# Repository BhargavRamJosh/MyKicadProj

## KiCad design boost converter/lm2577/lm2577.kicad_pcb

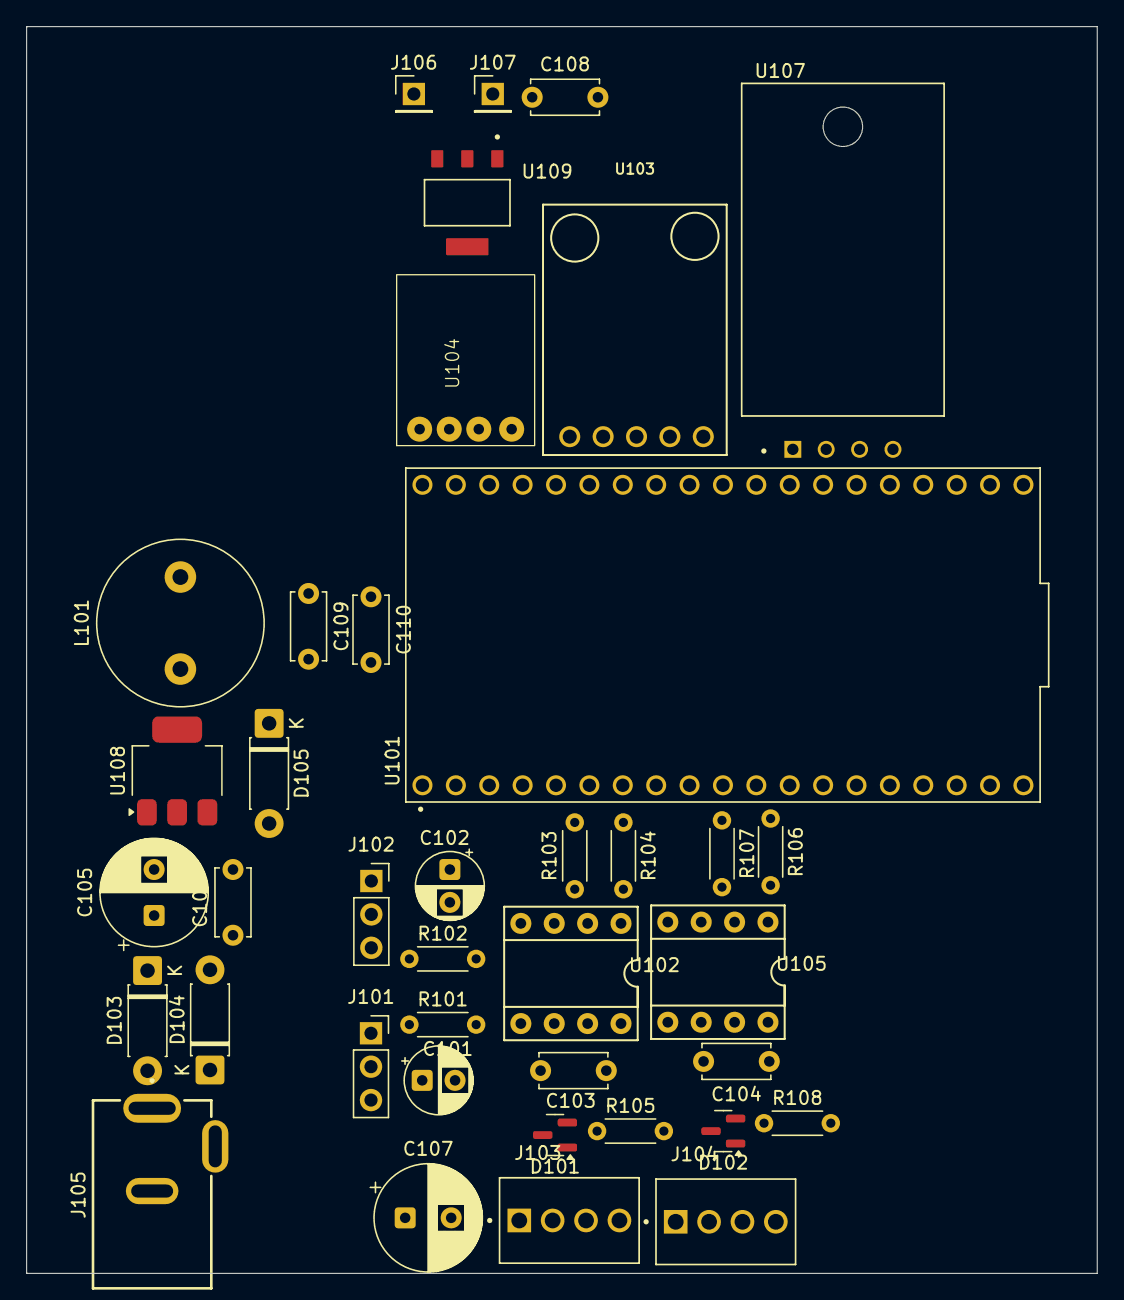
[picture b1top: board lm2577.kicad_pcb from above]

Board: 2 copper layers, 81.4 x 94.9 mm, 39 parts (0 on the bottom side), 24 nets, no tracks yet.

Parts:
C101: 10uF; CP_Radial_D5.0mm_P2.50mm
C102: 1uF; CP_Radial_D5.0mm_P2.50mm
C103, C104, C106, C110: 0.1uF; C_Disc_D5.0mm_W2.5mm_P5.00mm
C105: 100uF; CP_Radial_D8.0mm_P3.50mm
C107: 10uF; CP_Radial_D8.0mm_P3.50mm
C108: 10uF; C_Disc_D5.0mm_W2.5mm_P5.00mm
C109: 220uF; C_Disc_D5.0mm_W2.5mm_P5.00mm
D101, D102: SM712_SOT23; SOT-23
D103, D105: SS14; D_DO-41_SOD81_P7.62mm_Horizontal
D104: SMBJ15A; D_DO-41_SOD81_P7.62mm_Horizontal
J101, J102: Conn_01x03_Pin; PinSocket_1x03_P2.54mm_Vertical
J103, J104: Screw_Terminal_01x04; TE_282834-4
J105: DCJ200-10-A-XX-K_REVA; GCT_DCJ200-10-A-XX-K_REVA
J106, J107: Conn_01x01_Pin; PinHeader_1x01_P2.54mm_Vertical
L101: 22uH; L_Radial_D12.5mm_P7.00mm_Fastron_09HCP
R101, R102: 10K; R_Axial_DIN0204_L3.6mm_D1.6mm_P5.08mm_Horizontal
R103, R106: 3.9K; R_Axial_DIN0204_L3.6mm_D1.6mm_P5.08mm_Horizontal
R104, R107: 2K; R_Axial_DIN0204_L3.6mm_D1.6mm_P5.08mm_Horizontal
R105: 4.7K; R_Axial_DIN0204_L3.6mm_D1.6mm_P5.08mm_Horizontal
R108: 10k; R_Axial_DIN0204_L3.6mm_D1.6mm_P5.08mm_Horizontal
U101: NODEMCU-32S; MODULE_NODEMCU-32S
U102, U105: MAX485; DIL08
U103: ZC362800_
U104: BMP180; BMP180 breakout
U107: DHT22; XDCR_DHT22
U108: LM2596S-5; SOT-223-3_TabPin2
U109: AMS1117; SOT229P700X180-4N

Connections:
+5V: C103.1, C104.1, C107.1, C109.1, C110.1, J101.2, J102.2, J106.1, L101.2, U101.J1_19 (5V), U102.8 (VCC), U103.VCC, U105.8 (VCC), U109.3 (VI)
+12V: J103.1, J104.1
/ASoil: C101.2, R101.2, U101.J1_6 (IO35)
/Arain: C102.2, R102.2, U101.J1_5 (IO34)
/SCL: U101.J2_6 (IO21), U103.SCL
/SDA: U101.J2_3 (IO22), U103.SDA
/T&H: U101.J2_13 (IO4), U107.2 (DATA)
GND: C101.1, C102.1, C103.2, C104.2, C105.2, C106.2, C107.2, C108.2, C109.2, C110.2, D101.1 (A1), D101.3 (common), D102.1 (A1), D102.3 (common), D104.1 (K), D105.2 (A), J101.3, J102.3, J103.3, J103.4, J104.3, J104.4, J105.2, J105.3, R103.2, R105.2, R106.1, R108.2, U101.J1_14 (GND), U101.J2_1 (GND), U101.J2_7 (GND), U102.5 (GND), U102.6 (A), U103.GND, U105.5 (GND), U105.6 (A), U107.4 (GND), U108.3 (GND), U109.1 (ADJ)
unnamed: D101.2 (A2), J103.2, R105.1, U102.7 (B)
unnamed: D102.2 (A2), J104.2, R108.1, U105.7 (B)
unnamed: D103.2 (A), J105.1
unnamed: C105.1, C106.1, D103.1 (K), D104.2 (A), U108.1 (VIN)
unnamed: D105.1 (K), L101.1, U108.2 (OUT)
unnamed: J101.1, R101.1
unnamed: J102.1, R102.1
unnamed: C108.1, J107.1, U109.2 (VO)
unnamed: R104.1, U101.J2_12 (IO16)
unnamed: U101.J2_11 (IO17), U102.4 (DI)
unnamed: U101.J1_9 (IO25), U102.2 (RE), U102.3 (DE)
unnamed: R107.1, U101.J1_10 (IO26)
unnamed: U101.J1_11 (IO27), U105.4 (DI)
unnamed: U101.J1_8 (IO33), U105.2 (RE), U105.3 (DE)
unnamed: R103.1, R104.2, U102.1 (RO)
unnamed: R106.2, R107.2, U105.1 (RO)
